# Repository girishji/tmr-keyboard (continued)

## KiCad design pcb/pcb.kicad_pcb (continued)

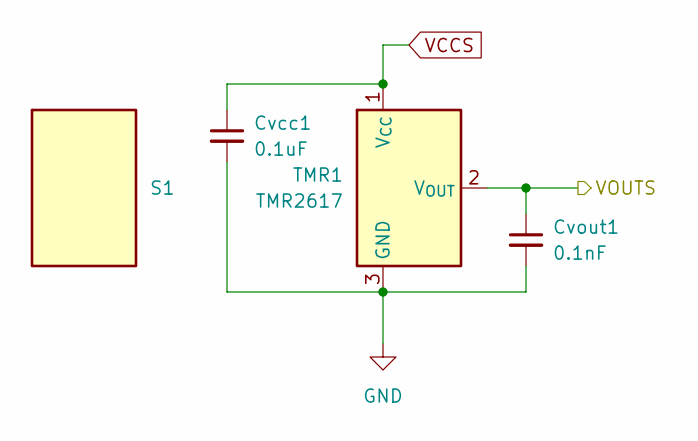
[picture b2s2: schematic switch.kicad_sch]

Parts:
Cvcc1: 0.1uF; C_0402_1005Metric
Cvout1: 0.1nF; C_0402_1005Metric
S1: Switch; Gateron_Switch_Lowpro
TMR1: TMR2617; SOT-23-3

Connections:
/ANA_01: Cvout1.1, TMR1.2 (V_{OUT}); also elsewhere on the board
GND: Cvcc1.2, Cvout1.2, TMR1.3 (GND); also elsewhere on the board
VCCS: Cvcc1.1, TMR1.1 (V_{CC}); also elsewhere on the board

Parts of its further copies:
Cvcc2, Cvcc3, Cvcc4, Cvcc5, Cvcc6, Cvcc7, Cvcc8, Cvcc9, Cvcc10, Cvcc11, Cvcc12, Cvcc13, Cvcc14, Cvcc15, Cvcc16, Cvcc17, Cvcc18, Cvcc19, Cvcc20, Cvcc21, Cvcc22, Cvcc23, Cvcc24, Cvcc25, Cvcc26, Cvcc27, Cvcc28, Cvcc29, Cvcc30, Cvcc31, Cvcc32, Cvcc33, Cvcc34, Cvcc35, Cvcc36, Cvcc37, Cvcc38, Cvcc39, Cvcc40, Cvcc41, Cvcc42, Cvcc43, Cvcc44, Cvcc45, Cvcc46, Cvcc47, Cvcc48, Cvcc49, Cvcc50, Cvcc51, Cvcc52, Cvcc53, Cvcc54, Cvcc55, Cvcc56, Cvcc57, Cvcc58, Cvcc59, Cvcc60, Cvcc61, Cvcc62, Cvcc63, Cvcc64, Cvcc65, Cvcc66, Cvcc67, Cvcc68, Cvcc69, Cvcc70, Cvcc71, Cvcc72: 0.1uF; C_0402_1005Metric
Cvout2, Cvout3, Cvout4, Cvout5, Cvout6, Cvout7, Cvout8, Cvout9, Cvout10, Cvout11, Cvout12, Cvout13, Cvout14, Cvout15, Cvout16, Cvout17, Cvout18, Cvout19, Cvout20, Cvout21, Cvout22, Cvout23, Cvout24, Cvout25, Cvout26, Cvout27, Cvout28, Cvout29, Cvout30, Cvout31, Cvout32, Cvout33, Cvout34, Cvout35, Cvout36, Cvout37, Cvout38, Cvout39, Cvout40, Cvout41, Cvout42, Cvout43, Cvout44, Cvout45, Cvout46, Cvout47, Cvout48, Cvout49, Cvout50, Cvout51, Cvout52, Cvout53, Cvout54, Cvout55, Cvout56, Cvout57, Cvout58, Cvout59, Cvout60, Cvout61, Cvout62, Cvout63, Cvout64, Cvout65, Cvout66, Cvout67, Cvout68, Cvout69, Cvout70, Cvout71, Cvout72: 0.1nF; C_0402_1005Metric
S2, S3, S4, S5, S6, S7, S8, S9, S10, S11, S12, S13, S14, S15, S16, S17, S18, S19, S20, S21, S22, S23, S24, S25, S26, S27, S28, S29, S30, S31, S32, S33, S34, S35, S36, S37, S38, S39, S40, S41, S42, S43, S44, S45, S46, S47, S48, S49, S50, S51, S52, S53, S54, S55, S56, S57, S58, S59, S60, S61, S62, S63, S64, S65, S66, S67, S68, S69, S70, S71, S72: Switch; Gateron_Switch_Lowpro
TMR2, TMR3, TMR4, TMR5, TMR6, TMR7, TMR8, TMR9, TMR10, TMR11, TMR12, TMR13, TMR14, TMR15, TMR16, TMR17, TMR18, TMR19, TMR20, TMR21, TMR22, TMR23, TMR24, TMR25, TMR26, TMR27, TMR28, TMR29, TMR30, TMR31, TMR32, TMR33, TMR34, TMR35, TMR36, TMR37, TMR38, TMR39, TMR40, TMR41, TMR42, TMR43, TMR44, TMR45, TMR46, TMR47, TMR48, TMR49, TMR50, TMR51, TMR52, TMR53, TMR54, TMR55, TMR56, TMR57, TMR58, TMR59, TMR60, TMR61, TMR62, TMR63, TMR64, TMR65, TMR66, TMR67, TMR68, TMR69, TMR70, TMR71, TMR72: TMR2617; SOT-23-3

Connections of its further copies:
/ANA_02: Cvout2.1, TMR2.2 (V_{OUT}); also elsewhere on the board
/ANA_03: Cvout3.1, TMR3.2 (V_{OUT}); also elsewhere on the board
/ANA_04: Cvout4.1, TMR4.2 (V_{OUT}); also elsewhere on the board
/ANA_05: Cvout5.1, TMR5.2 (V_{OUT}); also elsewhere on the board
/ANA_06: Cvout6.1, TMR6.2 (V_{OUT}); also elsewhere on the board
/ANA_07: Cvout7.1, TMR7.2 (V_{OUT}); also elsewhere on the board
/ANA_08: Cvout8.1, TMR8.2 (V_{OUT}); also elsewhere on the board
/ANA_09: Cvout9.1, TMR9.2 (V_{OUT}); also elsewhere on the board
/ANA_10: Cvout10.1, TMR10.2 (V_{OUT}); also elsewhere on the board
/ANA_11: Cvout11.1, TMR11.2 (V_{OUT}); also elsewhere on the board
/ANA_12: Cvout12.1, TMR12.2 (V_{OUT}); also elsewhere on the board
/ANA_13: Cvout13.1, TMR13.2 (V_{OUT}); also elsewhere on the board
/ANA_14: Cvout14.1, TMR14.2 (V_{OUT}); also elsewhere on the board
/ANA_15: Cvout15.1, TMR15.2 (V_{OUT}); also elsewhere on the board
/ANA_16: Cvout16.1, TMR16.2 (V_{OUT}); also elsewhere on the board
/ANA_17: Cvout17.1, TMR17.2 (V_{OUT}); also elsewhere on the board
/ANA_18: Cvout18.1, TMR18.2 (V_{OUT}); also elsewhere on the board
/ANA_19: Cvout19.1, TMR19.2 (V_{OUT}); also elsewhere on the board
/ANA_20: Cvout20.1, TMR20.2 (V_{OUT}); also elsewhere on the board
/ANA_21: Cvout21.1, TMR21.2 (V_{OUT}); also elsewhere on the board
/ANA_22: Cvout22.1, TMR22.2 (V_{OUT}); also elsewhere on the board
/ANA_23: Cvout23.1, TMR23.2 (V_{OUT}); also elsewhere on the board
/ANA_24: Cvout24.1, TMR24.2 (V_{OUT}); also elsewhere on the board
/ANA_25: Cvout25.1, TMR25.2 (V_{OUT}); also elsewhere on the board
/ANA_26: Cvout26.1, TMR26.2 (V_{OUT}); also elsewhere on the board
/ANA_27: Cvout27.1, TMR27.2 (V_{OUT}); also elsewhere on the board
/ANA_28: Cvout28.1, TMR28.2 (V_{OUT}); also elsewhere on the board
/ANA_29: Cvout29.1, TMR29.2 (V_{OUT}); also elsewhere on the board
/ANA_30: Cvout30.1, TMR30.2 (V_{OUT}); also elsewhere on the board
/ANA_31: Cvout31.1, TMR31.2 (V_{OUT}); also elsewhere on the board
/ANA_32: Cvout32.1, TMR32.2 (V_{OUT}); also elsewhere on the board
/ANA_33: Cvout33.1, TMR33.2 (V_{OUT}); also elsewhere on the board
/ANA_34: Cvout34.1, TMR34.2 (V_{OUT}); also elsewhere on the board
/ANA_35: Cvout35.1, TMR35.2 (V_{OUT}); also elsewhere on the board
/ANA_36: Cvout36.1, TMR36.2 (V_{OUT}); also elsewhere on the board
/ANA_37: Cvout37.1, TMR37.2 (V_{OUT}); also elsewhere on the board
/ANA_38: Cvout38.1, TMR38.2 (V_{OUT}); also elsewhere on the board
/ANA_39: Cvout39.1, TMR39.2 (V_{OUT}); also elsewhere on the board
/ANA_40: Cvout40.1, TMR40.2 (V_{OUT}); also elsewhere on the board
/ANA_41: Cvout41.1, TMR41.2 (V_{OUT}); also elsewhere on the board
/ANA_42: Cvout42.1, TMR42.2 (V_{OUT}); also elsewhere on the board
/ANA_43: Cvout43.1, TMR43.2 (V_{OUT}); also elsewhere on the board
/ANA_44: Cvout44.1, TMR44.2 (V_{OUT}); also elsewhere on the board
/ANA_45: Cvout45.1, TMR45.2 (V_{OUT}); also elsewhere on the board
/ANA_46: Cvout46.1, TMR46.2 (V_{OUT}); also elsewhere on the board
/ANA_47: Cvout47.1, TMR47.2 (V_{OUT}); also elsewhere on the board
/ANA_48: Cvout48.1, TMR48.2 (V_{OUT}); also elsewhere on the board
/ANA_49: Cvout49.1, TMR49.2 (V_{OUT}); also elsewhere on the board
/ANA_50: Cvout50.1, TMR50.2 (V_{OUT}); also elsewhere on the board
/ANA_51: Cvout51.1, TMR51.2 (V_{OUT}); also elsewhere on the board
/ANA_52: Cvout52.1, TMR52.2 (V_{OUT}); also elsewhere on the board
/ANA_53: Cvout53.1, TMR53.2 (V_{OUT}); also elsewhere on the board
/ANA_54: Cvout54.1, TMR54.2 (V_{OUT}); also elsewhere on the board
/ANA_55: Cvout55.1, TMR55.2 (V_{OUT}); also elsewhere on the board
/ANA_56: Cvout56.1, TMR56.2 (V_{OUT}); also elsewhere on the board
/ANA_57: Cvout57.1, TMR57.2 (V_{OUT}); also elsewhere on the board
/ANA_58: Cvout58.1, TMR58.2 (V_{OUT}); also elsewhere on the board
/ANA_59: Cvout59.1, TMR59.2 (V_{OUT}); also elsewhere on the board
/ANA_60: Cvout60.1, TMR60.2 (V_{OUT}); also elsewhere on the board
/ANA_61: Cvout61.1, TMR61.2 (V_{OUT}); also elsewhere on the board
/ANA_62: Cvout62.1, TMR62.2 (V_{OUT}); also elsewhere on the board
/ANA_63: Cvout63.1, TMR63.2 (V_{OUT}); also elsewhere on the board
/ANA_64: Cvout64.1, TMR64.2 (V_{OUT}); also elsewhere on the board
/ANA_65: Cvout65.1, TMR65.2 (V_{OUT}); also elsewhere on the board
/ANA_66: Cvout66.1, TMR66.2 (V_{OUT}); also elsewhere on the board
/ANA_67: Cvout67.1, TMR67.2 (V_{OUT}); also elsewhere on the board
/ANA_68: Cvout68.1, TMR68.2 (V_{OUT}); also elsewhere on the board
/ANA_69: Cvout69.1, TMR69.2 (V_{OUT}); also elsewhere on the board
/ANA_70: Cvout70.1, TMR70.2 (V_{OUT}); also elsewhere on the board
/ANA_71: Cvout71.1, TMR71.2 (V_{OUT}); also elsewhere on the board
/ANA_72: Cvout72.1, TMR72.2 (V_{OUT}); also elsewhere on the board
GND: Cvcc2.2, Cvcc3.2, Cvcc4.2, Cvcc5.2, Cvcc6.2, Cvcc7.2, Cvcc8.2, Cvcc9.2, Cvcc10.2, Cvcc11.2, Cvcc12.2, Cvcc13.2, Cvcc14.2, Cvcc15.2, Cvcc16.2, Cvcc17.2, Cvcc18.2, Cvcc19.2, Cvcc20.2, Cvcc21.2, Cvcc22.2, Cvcc23.2, Cvcc24.2, Cvcc25.2, Cvcc26.2, Cvcc27.2, Cvcc28.2, Cvcc29.2, Cvcc30.2, Cvcc31.2, Cvcc32.2, Cvcc33.2, Cvcc34.2, Cvcc35.2, Cvcc36.2, Cvcc37.2, Cvcc38.2, Cvcc39.2, Cvcc40.2, Cvcc41.2, Cvcc42.2, Cvcc43.2, Cvcc44.2, Cvcc45.2, Cvcc46.2, Cvcc47.2, Cvcc48.2, Cvcc49.2, Cvcc50.2, Cvcc51.2, Cvcc52.2, Cvcc53.2, Cvcc54.2, Cvcc55.2, Cvcc56.2, Cvcc57.2, Cvcc58.2, Cvcc59.2, Cvcc60.2, Cvcc61.2, Cvcc62.2, Cvcc63.2, Cvcc64.2, Cvcc65.2, Cvcc66.2, Cvcc67.2, Cvcc68.2, Cvcc69.2, Cvcc70.2, Cvcc71.2, Cvcc72.2, Cvout2.2, Cvout3.2, Cvout4.2, Cvout5.2, Cvout6.2, Cvout7.2, Cvout8.2, Cvout9.2, Cvout10.2, Cvout11.2, Cvout12.2, Cvout13.2, Cvout14.2, Cvout15.2, Cvout16.2, Cvout17.2, Cvout18.2, Cvout19.2, Cvout20.2, Cvout21.2, Cvout22.2, Cvout23.2, Cvout24.2, Cvout25.2, Cvout26.2, Cvout27.2, Cvout28.2, Cvout29.2, Cvout30.2, Cvout31.2, Cvout32.2, Cvout33.2, Cvout34.2, Cvout35.2, Cvout36.2, Cvout37.2, Cvout38.2, Cvout39.2, Cvout40.2, Cvout41.2, Cvout42.2, Cvout43.2, Cvout44.2, Cvout45.2, Cvout46.2, Cvout47.2, Cvout48.2, Cvout49.2, Cvout50.2, Cvout51.2, Cvout52.2, Cvout53.2, Cvout54.2, Cvout55.2, Cvout56.2, Cvout57.2, Cvout58.2, Cvout59.2, Cvout60.2, Cvout61.2, Cvout62.2, Cvout63.2, Cvout64.2, Cvout65.2, Cvout66.2, Cvout67.2, Cvout68.2, Cvout69.2, Cvout70.2, Cvout71.2, Cvout72.2, TMR2.3 (GND), TMR3.3 (GND), TMR4.3 (GND), TMR5.3 (GND), TMR6.3 (GND), TMR7.3 (GND), TMR8.3 (GND), TMR9.3 (GND), TMR10.3 (GND), TMR11.3 (GND), TMR12.3 (GND), TMR13.3 (GND), TMR14.3 (GND), TMR15.3 (GND), TMR16.3 (GND), TMR17.3 (GND), TMR18.3 (GND), TMR19.3 (GND), TMR20.3 (GND), TMR21.3 (GND), TMR22.3 (GND), TMR23.3 (GND), TMR24.3 (GND), TMR25.3 (GND), TMR26.3 (GND), TMR27.3 (GND), TMR28.3 (GND), TMR29.3 (GND), TMR30.3 (GND), TMR31.3 (GND), TMR32.3 (GND), TMR33.3 (GND), TMR34.3 (GND), TMR35.3 (GND), TMR36.3 (GND), TMR37.3 (GND), TMR38.3 (GND), TMR39.3 (GND), TMR40.3 (GND), TMR41.3 (GND), TMR42.3 (GND), TMR43.3 (GND), TMR44.3 (GND), TMR45.3 (GND), TMR46.3 (GND), TMR47.3 (GND), TMR48.3 (GND), TMR49.3 (GND), TMR50.3 (GND), TMR51.3 (GND), TMR52.3 (GND), TMR53.3 (GND), TMR54.3 (GND), TMR55.3 (GND), TMR56.3 (GND), TMR57.3 (GND), TMR58.3 (GND), TMR59.3 (GND), TMR60.3 (GND), TMR61.3 (GND), TMR62.3 (GND), TMR63.3 (GND), TMR64.3 (GND), TMR65.3 (GND), TMR66.3 (GND), TMR67.3 (GND), TMR68.3 (GND), TMR69.3 (GND), TMR70.3 (GND), TMR71.3 (GND), TMR72.3 (GND); also elsewhere on the board
VCCS: Cvcc2.1, Cvcc3.1, Cvcc4.1, Cvcc5.1, Cvcc6.1, Cvcc7.1, Cvcc8.1, Cvcc9.1, Cvcc10.1, Cvcc11.1, Cvcc12.1, Cvcc13.1, Cvcc14.1, Cvcc15.1, Cvcc16.1, Cvcc17.1, Cvcc18.1, Cvcc19.1, Cvcc20.1, Cvcc21.1, Cvcc22.1, Cvcc23.1, Cvcc24.1, Cvcc25.1, Cvcc26.1, Cvcc27.1, Cvcc28.1, Cvcc29.1, Cvcc30.1, Cvcc31.1, Cvcc32.1, Cvcc33.1, Cvcc34.1, Cvcc35.1, Cvcc36.1, Cvcc37.1, Cvcc38.1, Cvcc39.1, Cvcc40.1, Cvcc41.1, Cvcc42.1, Cvcc43.1, Cvcc44.1, Cvcc45.1, Cvcc46.1, Cvcc47.1, Cvcc48.1, Cvcc49.1, Cvcc50.1, Cvcc51.1, Cvcc52.1, Cvcc53.1, Cvcc54.1, Cvcc55.1, Cvcc56.1, Cvcc57.1, Cvcc58.1, Cvcc59.1, Cvcc60.1, Cvcc61.1, Cvcc62.1, Cvcc63.1, Cvcc64.1, Cvcc65.1, Cvcc66.1, Cvcc67.1, Cvcc68.1, Cvcc69.1, Cvcc70.1, Cvcc71.1, Cvcc72.1, TMR2.1 (V_{CC}), TMR3.1 (V_{CC}), TMR4.1 (V_{CC}), TMR5.1 (V_{CC}), TMR6.1 (V_{CC}), TMR7.1 (V_{CC}), TMR8.1 (V_{CC}), TMR9.1 (V_{CC}), TMR10.1 (V_{CC}), TMR11.1 (V_{CC}), TMR12.1 (V_{CC}), TMR13.1 (V_{CC}), TMR14.1 (V_{CC}), TMR15.1 (V_{CC}), TMR16.1 (V_{CC}), TMR17.1 (V_{CC}), TMR18.1 (V_{CC}), TMR19.1 (V_{CC}), TMR20.1 (V_{CC}), TMR21.1 (V_{CC}), TMR22.1 (V_{CC}), TMR23.1 (V_{CC}), TMR24.1 (V_{CC}), TMR25.1 (V_{CC}), TMR26.1 (V_{CC}), TMR27.1 (V_{CC}), TMR28.1 (V_{CC}), TMR29.1 (V_{CC}), TMR30.1 (V_{CC}), TMR31.1 (V_{CC}), TMR32.1 (V_{CC}), TMR33.1 (V_{CC}), TMR34.1 (V_{CC}), TMR35.1 (V_{CC}), TMR36.1 (V_{CC}), TMR37.1 (V_{CC}), TMR38.1 (V_{CC}), TMR39.1 (V_{CC}), TMR40.1 (V_{CC}), TMR41.1 (V_{CC}), TMR42.1 (V_{CC}), TMR43.1 (V_{CC}), TMR44.1 (V_{CC}), TMR45.1 (V_{CC}), TMR46.1 (V_{CC}), TMR47.1 (V_{CC}), TMR48.1 (V_{CC}), TMR49.1 (V_{CC}), TMR50.1 (V_{CC}), TMR51.1 (V_{CC}), TMR52.1 (V_{CC}), TMR53.1 (V_{CC}), TMR54.1 (V_{CC}), TMR55.1 (V_{CC}), TMR56.1 (V_{CC}), TMR57.1 (V_{CC}), TMR58.1 (V_{CC}), TMR59.1 (V_{CC}), TMR60.1 (V_{CC}), TMR61.1 (V_{CC}), TMR62.1 (V_{CC}), TMR63.1 (V_{CC}), TMR64.1 (V_{CC}), TMR65.1 (V_{CC}), TMR66.1 (V_{CC}), TMR67.1 (V_{CC}), TMR68.1 (V_{CC}), TMR69.1 (V_{CC}), TMR70.1 (V_{CC}), TMR71.1 (V_{CC}), TMR72.1 (V_{CC}); also elsewhere on the board

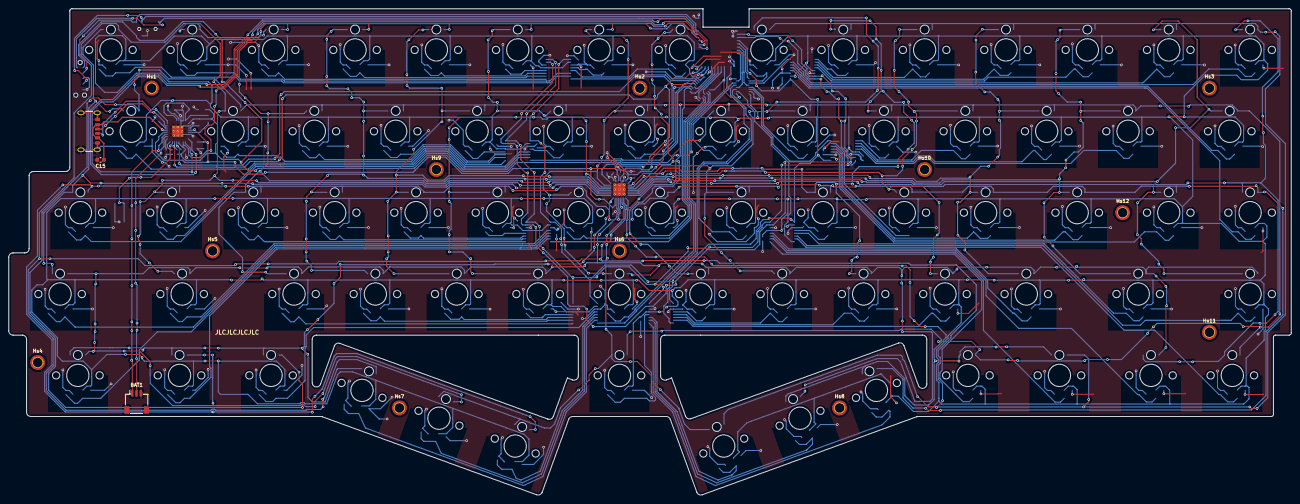
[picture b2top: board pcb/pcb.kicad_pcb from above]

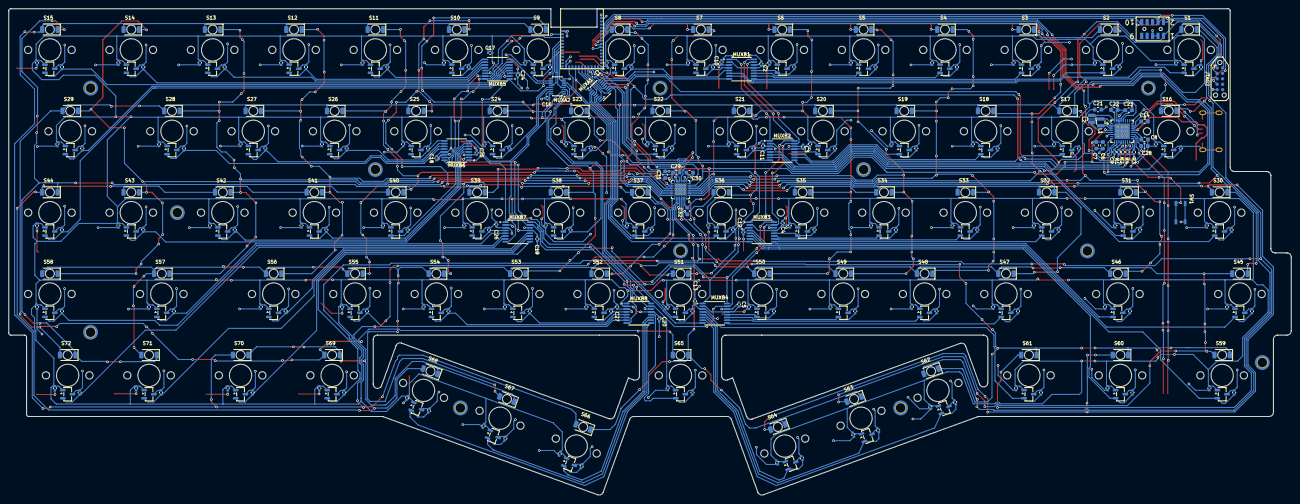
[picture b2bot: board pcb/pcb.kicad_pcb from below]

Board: 2 copper layers, 299.5 x 113.5 mm, 431 parts (341 on the bottom side), 140 nets.
